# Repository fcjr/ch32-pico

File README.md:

# ch32-pico

A tiny RISC-V dev board in the Pico's footprint, with USB-C, 37 GPIOs and
USB Power Delivery you control from your own code. Built by Left Shift
Logical around the WCH CH32X035.

## Why you might want one

- **Plug in and program.** The chip's factory USB bootloader loads your
  application straight over USB-C. No programmer, no adapter.
- **Ask your charger for more.** The CH32X035 speaks USB-PD natively. Your
  firmware can request 5, 9, 12, 15 or 20 V from a PD supply, and that voltage
  appears on pin 40 for whatever you're driving.
- **Plenty of pins.** 26 GPIOs on the headers with UART, I2C, SPI, PWM and
  three ADC inputs, plus ten more on pads underneath, including op-amp and two
  extra ADC inputs.
- **Fits where a Pico fits.** Same 21 × 51 mm outline, same 40 header
  positions, castellated edges for soldering straight onto a carrier.
- **See what it's doing.** Labelled probe pads for VBUS, the CC lines, USB data
  and the LED, and a RESET and BOOT button on the bottom edge.
- **Open.** MIT-licensed software, CERN-OHL-P hardware, and the whole design
  is Python you can read and regenerate.

## Read this before you connect anything to pin 40

Pin 40 is the USB VBUS rail, exactly as on the Pico. It's 5 V when you plug in,
and it stays 5 V unless your firmware asks the supply for more. If it does, pin
40 carries that higher voltage, up to 20 V, with nothing in between to stop it.
So:

- Only request a voltage your carrier board can take.
- Don't feed power into pin 40 while a USB cable is connected.
- A short on pin 40 relies on your charger's protection, not the board's.

Pin 39 (VSYS) is still a 4.3–5.5 V input and pin 36 is still a fixed 3.3 V
output, so a plain 5 V Pico carrier works as long as your firmware leaves the
PD voltage alone.

## A few pins are different from the Pico

| Pin | On a Pico | Here |
|---|---|---|
| 35 | ADC_VREF | Not connected until you bridge solder jumper SJ1 (front, below the chip); then it's PC7 |
| 37 | 3V3_EN | Ground it to switch the 3.3 V regulator off. Released, it sits at the input voltage (up to 20 V) through 100 kΩ, so drive it with a switch or an open-drain output, never a logic input |
| 40 | VBUS, 5 V | VBUS, 5 V or whatever PD voltage you negotiate |

The GPIO labels on the back use the chip's own names (PA0, PB10, …), not Pico
GP numbers. The full pinout and peripheral map are in the
[design notes](docs/design.md#header-allocation).

## Where things stand

This is a prototype. The design passes every automated check we have, but no
boards have been built yet, so the 3 A power target, the USB-PD application
firmware and the thermal and surge behaviour are all unverified. Treat it as a
board to build and test, not one to put in a product. Open items are tracked in
the [qualification plan](docs/power-qualification.md).

## Build your own

With `uv`, `just` and KiCad 10 installed:

```sh
just jlcpcb
```

That checks the design and produces the Gerbers, BOM and placement file for a
JLCPCB order of twenty boards. See [build instructions](docs/build.md) and the
[manufacturing notes](docs/manufacturing.md) for details, and the
[parts review](docs/factory-review.md) for stock and cost at the last check.

## Learn more

- [Design, pinout and limits](docs/design.md)
- [Power qualification plan](docs/power-qualification.md)
- [PD firmware policy](firmware/pd/README.md)
- [Parts and factory review](docs/factory-review.md)
- [Licensing](docs/licensing.md)

Software: [MIT](LICENSES/MIT.txt). Hardware:
[CERN-OHL-P-2.0](LICENSES/CERN-OHL-P-2.0.txt).

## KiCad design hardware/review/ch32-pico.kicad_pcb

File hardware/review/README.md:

# ch32-pico layout checkpoint

Open [ch32-pico.kicad_pcb](ch32-pico.kicad_pcb) in KiCad 10.0.6.
The local footprint table points to the vendored library.

The [validation report](validation.json) records the source checks, DRC,
connectivity, routing comparison and outstanding prototype work.
Layer previews: [front](front.svg), [back](back.svg),
[ground](ground.svg), [inner power/signals](power.svg).

See [build instructions](../../docs/build.md) for regenerating this checkpoint
and [manufacturing](../../docs/manufacturing.md) for fabrication outputs.

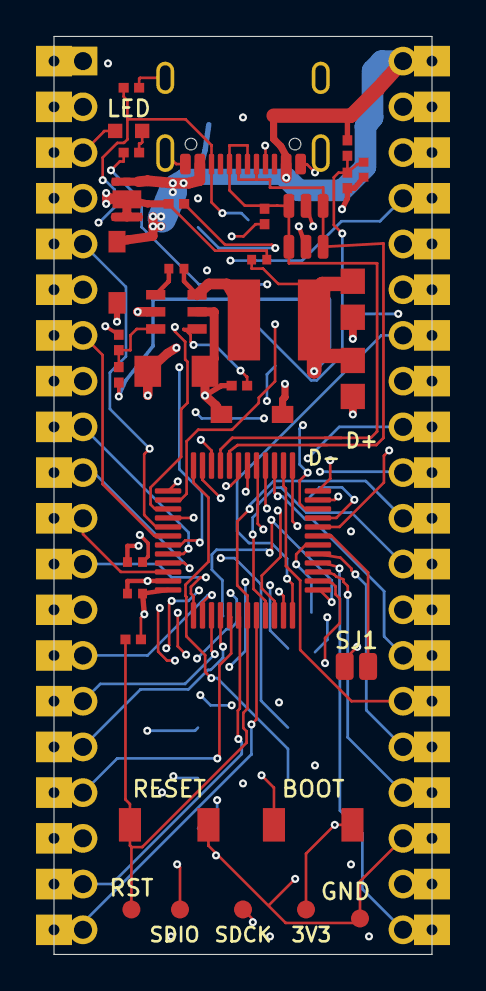
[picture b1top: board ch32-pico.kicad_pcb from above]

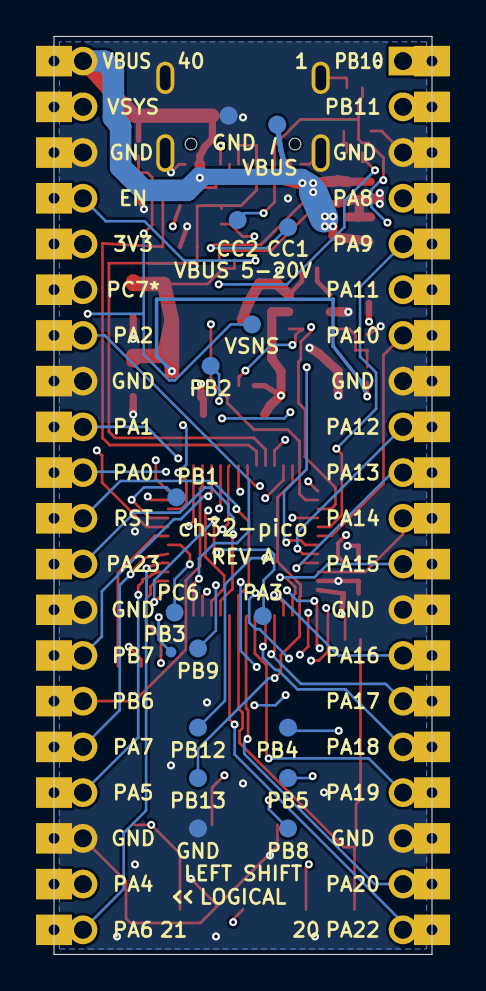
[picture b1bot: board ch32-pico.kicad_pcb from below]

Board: 4 copper layers, 21.0 x 51.0 mm, 55 parts (17 on the bottom side), 58 nets.

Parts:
C1: 10uF / 50V; C1206
C2, C3: 22uF / 10V; C0805
C4, C6, C9, C11: 100nF / 50V; C0402
C7: 1uF; C0402
D1, D4: B5819W; SOD-123_L2.7-W1.6-LS3.7-RD-1
D2: USBLC6-2SC6; SOT-23-6
D3: RED / STATUS; LED-SMD_L1.6-W0.8-R-RD
D5: TVS2200DRVR; WSON-6_L2.0-W2.0-P0.65-BL-EP
J1: PICO 40-PIN; Pico_Header
J2: GT-USB-7010ASV; USB_C_Receptacle_G-Switch_GT-USB-7010
L1: 4.7uH; IND-SMD_L5.0-W5.0-P3.60_SMNR5040
R1, R15: 100k; R0402
R2, R10: 10k; R0402
R3, R4: 5.1k; R0402
R11: 1k; R0402
R12: 4.7k; R0402
R13: 47k; R0402
R14: 15k; R0402
SJ1: PC7 OPTION; SolderJumper_Open
SW1: RESET; SW-SMD_L3.9-W3.0-P4.45
SW2: BOOT; SW-SMD_L3.9-W3.0-P4.45
TP1: SDIO; TestPad_1mm
TP2: SDCK; TestPad_1mm
TP3: 3V3_OUT; TestPad_1mm
TP4, TP13, TP16: GND; TestPad_1mm
TP5: PA21; TestPad_1mm
TP6: PC6; TestPad_1mm
TP7: PB4; TestPad_1mm
TP8: PB5; TestPad_1mm
TP9: PB8; TestPad_1mm
TP10: PB9; TestPad_1mm
TP11: PB12; TestPad_1mm
TP12: PB13; TestPad_1mm
TP14: PA3; TestPad_1mm
TP15: VBUS; TestPad_1mm
TP17: VBUS_SENSE; TestPad_1mm
TP18: PB1; TestPad_1mm
TP19: CC1; TestPad_1mm
TP20: CC2; TestPad_1mm
TP21: PB2; TestPad_1mm
TP22: STATUS_LED; TestPad_0.6mm
TP23: USB_DP; USB_Probe_Inline
TP24: USB_DM; USB_Probe_Inline
U1: CH32X035C8T6; LQFP-48_7x7mm_P0.5mm
U4: SY8301ABC; SOT-23-6_L2.9-W1.6-P0.95-LS2.8-BL

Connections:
3V3_EN: J1.37, R15.2, U4.4
3V3_OUT: C2.1, C3.1, C6.1, C7.1, C11.1, D2.5, J1.36, L1.2, R10.2, R13.1, SW2.2, TP3.1, U1.48
BOOT_PULLUP: R12.2, SW2.1
BUCK_BST: C4.1, U4.1
BUCK_FB: R13.2, R14.1, U4.3
BUCK_SW: C4.2, L1.1, U4.6
CC1: J2.A5, R3.1, TP19.1, U1.38
CC2: J2.B5, R4.1, TP20.1, U1.39
GND: C1.2, C2.2, C3.2, C6.2, C7.2, C9.2, C11.2, D2.2, D3.2, D5.1, D5.2, D5.3, D5.7, J1.3, J1.8, J1.13, J1.18, J1.23, J1.28, J1.33, J1.38, J2.13, J2.14, J2.15, J2.16, J2.A1B12, J2.B1A12, R2.2, R3.2, R4.2, R14.2, SW1.2, TP4.1, TP13.1, TP16.1, U1.47, U4.2
GPIO35: J1.35, SJ1.1
LED_A: D3.1, R11.2
PA0: J1.31, U1.10
PA1: J1.32, U1.11
PA2: J1.34, U1.12
PA3: TP14.1, U1.13
PA4: J1.22, U1.14
PA5: J1.24, U1.15
PA6: J1.21, U1.16
PA7: J1.25, U1.17
PA8: J1.4, U1.40
PA9: J1.5, U1.41
PA10: J1.7, U1.42
PA11: J1.6, U1.43
PA12: J1.9, U1.44
PA13: J1.10, U1.45
PA14: J1.11, U1.46
PA15: J1.12, U1.1
PA16: J1.14, U1.2
PA17: J1.15, U1.3
PA18: J1.16, U1.4
PA19: J1.17, U1.5
PA20: J1.19, U1.6
PA21: J1.30, R10.1, SW1.1, TP5.1, U1.7
PA22: J1.20, U1.8
PA23: J1.29, U1.9
PB1: TP18.1, U1.21
PB2: TP21.1, U1.22
PB4: TP7.1, U1.24
PB5: TP8.1, U1.25
PB6: J1.26, U1.26
PB7: J1.27, U1.27
PB8: TP9.1, U1.28
PB9: TP10.1, U1.29
PB10: J1.1, U1.30
PB11: J1.2, U1.31
PB12: TP11.1, U1.35
PB13: TP12.1, U1.36
PC6: TP6.1, U1.18
PC7: SJ1.2, U1.19
SDCK: TP2.1, U1.37
SDIO: TP1.1, U1.34
STATUS_LED: R11.1, TP22.1, U1.23
USB_DM: D2.3, D2.4, J2.A7, J2.B7, TP24.1, U1.32
USB_DP: D2.1, D2.6, J2.A6, J2.B6, R12.1, TP23.1, U1.33
VBUS: D1.2, D5.4, D5.5, D5.6, J1.40, J2.A4B9, J2.B4A9, R1.1, TP15.1
VBUS_SENSE: C9.1, R1.2, R2.1, TP17.1, U1.20
VIN_SYS: C1.1, D1.1, D4.1, R15.1, U4.5
VSYS: D4.2, J1.39

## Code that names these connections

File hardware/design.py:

# SPDX-License-Identifier: MIT
# Copyright (c) 2026 ch32-pico contributors
"""Mechanical contract and proposed electrical allocation.

Coordinates are mm, viewed from the component side with USB at the top.
Origin is the upper-left board corner. The netlist is in hardware/circuit.py.
"""
from __future__ import annotations


from dataclasses import dataclass

BOARD_REVISION = 'A'


@dataclass(frozen=True)
class Mechanical:
    width: float = 21.0
    length: float = 51.0
    thickness: float = 1.0
    pitch: float = 2.54
    row_spacing: float = 17.78
    header_drill: float = 1.0
    header_pad: float = 1.6
    mounting_drill: float = 2.1

    def position(self, pin: int) -> tuple[float, float]:
        if not 1 <= pin <= 40:
            raise ValueError(f"Invalid Pico pin: {pin}")
        x = (self.width - self.row_spacing) / 2
        y = (self.length - 19 * self.pitch) / 2
        if pin <= 20:
            return round(x, 3), round(y + (pin - 1) * self.pitch, 3)
        return round(self.width - x, 3), round(y + (40 - pin) * self.pitch, 3)

    @property
    def mounting_holes(self) -> tuple[tuple[float, float], ...]:
        return ()


@dataclass(frozen=True)
class HeaderPin:
    number: int
    pico: str
    proposed: str
    function: str


MECHANICAL = Mechanical()

# Pin 40 follows USB VBUS directly, like the Pico: 5 V until PD negotiates more.
MCU_PART = 'C29779902'
MCU_MPN = 'CH32X035C8T6'
POWER_REQUIREMENTS = {
    "topology": "fixed-3v3-buck-and-direct-pd-vbus",
    "vsys_min_v": 4.3, "vsys_max_v": 5.5, "output_v": 3.3,
    "header_current_goal_ma": 50, "usb_backfeed_allowed": False,
    "pd_voltage_steps_v": (5, 9, 12, 15, 20),
    "pd_output_current_goal_ma": 3000,
    "pd_output_location": "Pico pin 40, unswitched USB VBUS; 5 V until PD negotiates higher",
}

# WCH CH32X035 datasheet, LQFP48 pin diagram and table 2-1.
TARGET_PINS = dict(zip(
    ('PA15 PA16 PA17 PA18 PA19 PA20 PA21 PA22 PA23 PA0 PA1 PA2 '
     'PA3 PA4 PA5 PA6 PA7 PC6 PC7 PB0 PB1 PB2 PB3 PB4 PB5 PB6 PB7 '
     'PB8 PB9 PB10 PB11 PC16 PC17 PC18 PB12 PB13 PC19 PC14 PC15 '
     'PA8 PA9 PA10 PA11 PA12 PA13 PA14 VSS VDD').split(),range(1,49)))

# Unpopulated underside expansion pads: seven free GPIOs.
EXPANSION_SIGNALS = ('PC6', 'PB4', 'PB5', 'PB8', 'PB9', 'PB12', 'PB13')

# Pins reserved for USB, PD, recovery and board status.
INTERNAL_SIGNALS = {
    'PC16':'USB_DM', 'PC17':'USB_DP', 'PC14':'CC1', 'PC15':'CC2',
    'PC18':'SDIO', 'PC19':'SDCK', 'PB0':'VBUS_SENSE', 'PB3':'STATUS_LED',
}

HEADER = tuple(HeaderPin(*row) for row in (
    (1, "GP0", "PB10", "USART1 TX, default mapping"),
    (2, "GP1", "PB11", "USART1 RX, default mapping"),
    (3, "GND", "GND", "Ground"),
    (4, "GP2", "PA8", "GPIO"),
    (5, "GP3", "PA9", "GPIO"),
    (6, "GP4", "PA11", "I2C SDA, default mapping"),
    (7, "GP5", "PA10", "I2C SCL, default mapping"),
    (8, "GND", "GND", "Ground"),
    (9, "GP6", "PA12", "GPIO"),
    (10, "GP7", "PA13", "GPIO"),
    (11, "GP8", "PA14", "GPIO"),
    (12, "GP9", "PA15", "GPIO; USART2 TX remap 2"),
    (13, "GND", "GND", "Ground"),
    (14, "GP10", "PA16", "GPIO; USART2 RX remap 2"),
    (15, "GP11", "PA17", "GPIO"),
    (16, "GP12", "PA18", "GPIO"),
    (17, "GP13", "PA19", "GPIO"),
    (18, "GND", "GND", "Ground"),
    (19, "GP14", "PA20", "GPIO"),
    (20, "GP15", "PA22", "GPIO"),
    (21, "GP16", "PA6", "SPI MISO, default mapping"),
    (22, "GP17", "PA4", "SPI NSS or software chip select"),
    (23, "GND", "GND", "Ground"),
    (24, "GP18", "PA5", "SPI SCK, default mapping"),
    (25, "GP19", "PA7", "SPI MOSI, default mapping"),
    (26, "GP20", "PB6", "GPIO"),
    (27, "GP21", "PB7", "GPIO"),
    (28, "GND", "GND", "Ground"),
    (29, "GP22", "PA23", "GPIO"),
    (30, "RUN", "PA21", "RST input; preserve reset option-byte configuration"),
    (31, "GP26 / ADC0", "PA0", "ADC channel 0"),
    (32, "GP27 / ADC1", "PA1", "ADC channel 1"),
    (33, "AGND", "GND", "Continuous ground plane"),
    (34, "GP28 / ADC2", "PA2", "ADC channel 2"),
    (35, "ADC_VREF", "GPIO35", "Isolated by open SJ1; bridge SJ1 for PC7 GPIO / one-wire PIOC"),
    (36, "3V3_OUT", "3V3_OUT", "Fixed 3.3 V output; prototype load rating pending"),
    (37, "3V3_EN", "3V3_EN", "Pull low to shut down 3.3 V; release for automatic startup"),
    (38, "GND", "GND", "Ground"),
    (39, "VSYS", "VSYS", "4.3-5.5 V input only; diode-isolated from VBUS"),
    (40, "VBUS", "VBUS", "USB VBUS, 5 V by default; follows any higher PD contract firmware requests"),
))


def validate() -> None:
    if [p.number for p in HEADER] != list(range(1,41)):
        raise ValueError("Header must contain pins 1 through 40 exactly once")
    signals=[p.proposed for p in HEADER if p.proposed in TARGET_PINS]
    if len(set(signals)) != len(signals) or len(signals)!=27:
        raise ValueError("Require 26 distinct GPIOs and one reset input")
    if set(signals) & set(INTERNAL_SIGNALS):
        raise ValueError("Board status, USB, PD and debug must not share header GPIO")
    if any(p.proposed!='GND' for p in HEADER if p.pico in {'GND','AGND'}):
        raise ValueError("Pico ground positions must remain ground")
    if HEADER[34].proposed != 'GPIO35':
        raise ValueError('Pin 35 must remain on the isolated jumper-side net')

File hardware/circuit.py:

# SPDX-License-Identifier: MIT
# Copyright (c) 2026 ch32-pico contributors
"""Electrical source. Every terminal has an explicit net or NC.

CH32X035 is the only MCU and PD controller. Header pin 40 is USB VBUS,
unswitched like the Pico's; the fixed buck powers only the MCU and 3V3 header.
Prototype, not released.
"""
from __future__ import annotations
from dataclasses import dataclass
from .diagnostics import DIAGNOSTICS
from .design import HEADER, TARGET_PINS, INTERNAL_SIGNALS, MCU_PART, EXPANSION_SIGNALS

@dataclass(frozen=True)
class Component:
    ref: str
    part: str
    nets: dict[str, str | None]
    section: str
    value: str = ''
    note: str = ''
    fitted: bool = True


def two(ref, part, a, b, section, value='', note=''):
    return Component(ref,part,{'1':a,'2':b},section,value,note)


def mcu_nets():
    nets={str(n):None for n in TARGET_PINS.values()}
    for p in HEADER:
        if p.proposed in TARGET_PINS:nets[str(TARGET_PINS[p.proposed])]=p.proposed
    for port,net in INTERNAL_SIGNALS.items():nets[str(TARGET_PINS[port])]=net
    for port in EXPANSION_SIGNALS:
        if port in TARGET_PINS:nets[str(TARGET_PINS[port])]=port
    for d in DIAGNOSTICS:
        if d.net in TARGET_PINS:nets[str(TARGET_PINS[d.net])]=d.net
    nets[str(TARGET_PINS['PC7'])]='PC7'  # SJ1 optional header connection
    nets['47']='GND';nets['48']='3V3_OUT'
    return nets


COMPONENTS = (
    *(Component(f'#FLG{i:02}', 'POWER_FLAG', {'1':n}, 'power', n, fitted=False)
      for i,n in enumerate(('GND','VBUS','VSYS','VIN_SYS','3V3_OUT'),1)),
    # Diode OR feeds ONLY the control supply. Header VSYS never sees PD VBUS.
    two('D1','C8598','VIN_SYS','VBUS','power','B5819W','Cathode pin 1; control-rail current only'),
    two('D4','C8598','VIN_SYS','VSYS','power','B5819W','Cathode pin 1; blocks PD backfeed into header 39'),
    Component('U4','C2927130',{'1':'BUCK_BST','2':'GND','3':'BUCK_FB','4':'3V3_EN','5':'VIN_SYS','6':'BUCK_SW'},'power',note='SY8301 2 MHz buck, 0.8 V reference; EN pulled up to VIN_SYS by R15, header 37 grounds it to shut down'),
    two('R13','C25792','3V3_OUT','BUCK_FB','power','47k','Feedback divider top; senses the output capacitors through a dedicated trace'),
    two('R14','C25756','BUCK_FB','GND','power','15k','Feedback divider bottom: 0.8 V x (1 + 47/15) = 3.307 V'),
    two('R15','C25741','VIN_SYS','3V3_EN','power','100k','EN pull-up to the diode-OR node so VSYS-only power still starts the regulator'),
    two('L1','C48496','BUCK_SW','3V3_OUT','power','4.7uH'),
    two('C1','C13585','VIN_SYS','GND','power','10uF / 50V','Input capacitance/inrush requires bench qualification'),
    two('C2','C29277','3V3_OUT','GND','power','22uF / 10V'),
    two('C3','C29277','3V3_OUT','GND','power','22uF / 10V'),
    two('C4','C307331','BUCK_BST','BUCK_SW','power','100nF / 50V'),
    # Native USB. CC pins have independent external Rd, even while MCU is blank.
    Component('J2','C2988369',{'A1B12':'GND','B1A12':'GND',**{str(i):'GND' for i in range(13,17)},'A4B9':'VBUS','B4A9':'VBUS','A5':'CC1','B5':'CC2','A6':'USB_DP','B6':'USB_DP','A7':'USB_DM','B7':'USB_DM','A8':None,'B8':None},'usb',note='G-Switch GT-USB-7010ASV: 3 A VBUS contacts, equal to the board target; the 5 A AN variant shares the copper; qualify cable and assembly fit'),
    two('R3','C25905','CC1','GND','usb','5.1k'),
    two('R4','C25905','CC2','GND','usb','5.1k'),
    Component('D2','C7519',{'1':'USB_DP','2':'GND','3':'USB_DM','4':'USB_DM','5':'3V3_OUT','6':'USB_DP'},'usb',note='ESD rail is 3.3 V, NEVER negotiated VBUS'),
    two('C11','C307331','3V3_OUT','GND','usb','100nF / 50V'),
    # Pin 40 is direct VBUS. D5 clamps cable hot-plug ringing below U4's
    # 32 V operating limit when a source is already at a higher PD voltage.
    Component('D5','C523793',{'1':'GND','2':'GND','3':'GND','4':'VBUS','5':'VBUS','6':'VBUS','7':'GND'},
        'pd',note='TVS2200; 22 V standoff, 28.35 V specified hot surge clamp; no continuous regeneration rating'),
    two('R1','C25741','VBUS','VBUS_SENSE','pd','100k'),
    two('R2','C25744','VBUS_SENSE','GND','pd','10k'),
    two('C9','C307331','VBUS_SENSE','GND','pd','100nF / 50V'),
    Component('U1',MCU_PART,mcu_nets(),'target',note='Only MCU; native USB, CC1/CC2 PD PHY, SDI recovery'),
    two('C6','C307331','3V3_OUT','GND','target','100nF / 50V','Adjacent to U1 pins 48/47'),
    two('C7','C52923','3V3_OUT','GND','target','1uF'),
    two('R10','C25744','PA21','3V3_OUT','target','10k','Keep PA21 configured as reset in option bytes'),
    two('R11','C11702','STATUS_LED','LED_A','target','1k'),
    two('D3','C2286','LED_A','GND','target','RED / STATUS'),
    two('R12','C25900','USB_DP','BOOT_PULLUP','target','4.7k','WCH reference download-button pull-up'),
    two('SW1','C49234124','PA21','GND','target','RESET'),
    two('SW2','C49234124','BOOT_PULLUP','3V3_OUT','target','BOOT','Hold during power-up, release before USB ISP'),
    Component('J1','PICO_HEADER',{str(p.number):None if p.proposed=='NC' else p.proposed for p in HEADER},'header','PICO 40-PIN','Pin 40 is USB VBUS: 5 V by default, higher only after PD negotiation',False),
    Component('SJ1','SOLDER_JUMPER',{'1':'GPIO35','2':'PC7'},'header','PC7 OPTION','Normally open; user solder bridge connects header 35 to PC7. No factory paste or assembly.',False),
    *(Component(f'TP{i}','TESTPAD',{'1':n},'header',n,'SDI recovery / measurement pad',False)
      for i,n in enumerate(('SDIO','SDCK','3V3_OUT','GND','PA21'),1)),
    *(Component(f'TP{i}','TESTPAD',{'1':n},'header',n,'Underside expansion solder pad',False)
      for i,n in enumerate((*EXPANSION_SIGNALS,'GND'),6)),
    *(Component(d.ref,d.part,{'1':d.net},'header',d.net,
                'Diagnostic probe contact; no paste or fitted component',False) for d in DIAGNOSTICS),
)
SECTIONS={'power':'Fixed 3.3 V control supply','usb':'Native USB-C and PD CC interface',
          'pd':'VBUS clamp and sense','target':'CH32X035 and USB boot entry',
          'header':'Pico headers and SDI recovery'}
